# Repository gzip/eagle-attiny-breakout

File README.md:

# AVR ATtiny85 Development Board

This is a flexible development board for the 8 pin family of AVR ATtiny devices. It's like Arduino's little brother. It can be programmed using [Little Wire](https://github.com/gzip/Little-Wire/tree/master), USBasp, Arduino as ISP, etc.

- Arduino compatible via [Arduino-Tiny](https://code.google.com/p/arduino-tiny/) or [Code Bender](https://codebender.cc/)
- All pins exposed via headers
- Header for external power
- Wide operating voltage - 2.7 - 5.5 volts
- 4 channel power bus with filtering capacitors
- Space for an optional resonator
- Mounting holes
- No LED to save power
- Onboard reset switch

# Availability

Currently available in kit form at [Tindie](https://www.tindie.com/products/gzip/avr-attiny85-development-board-kit/).

# Installing

See [Installing](Installing.md) for driver and environment installation.

# License

This hardware is licensed under [Creative Commons Share Alike](http://creativecommons.org/licenses/by-sa/4.0/).

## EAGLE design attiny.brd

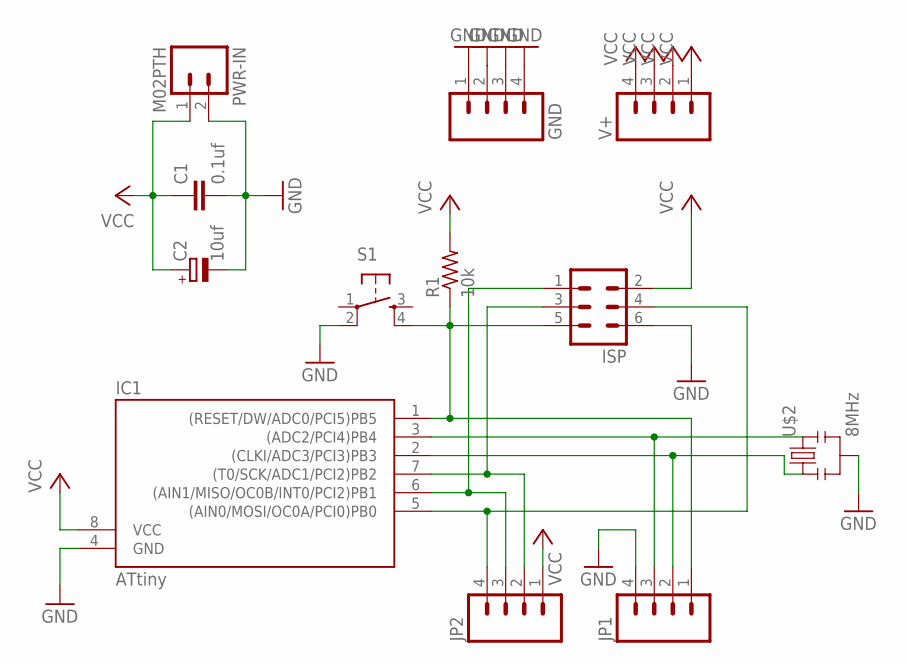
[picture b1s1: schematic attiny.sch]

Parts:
C1: 0.1uf; C025-025X050
C2: 10uf; E2-4
GND: M04PTH; 1X04
IC1: ATtiny; DIL08
ISP: MA03-2
JP1, JP2: M04PTH; 1X04
PWR-IN: M02PTH; 1X02
R1: 10k; 0204/7
S1: TAC_SWITCHPTH; TACTILE-PTH
U$2: 8MHz; RESONATOR-PTH
V+: M04PTH; 1X04

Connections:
GND: C1.2, C2.-, GND.1, GND.2, GND.3, GND.4, IC1.4 (GND), ISP.6, JP1.4, PWR-IN.2, S1.2, U$2.2
unnamed: IC1.2 ((CLKI/ADC3/PCI3)PB3), JP1.2, U$2.1
unnamed: IC1.1 ((RESET/DW/ADC0/PCI5)PB5), ISP.5, JP1.1, R1.1, S1.4
unnamed: IC1.7 ((T0/SCK/ADC1/PCI2)PB2), ISP.3, JP2.2
unnamed: IC1.6 ((AIN1/MISO/OC0B/INT0/PCI2)PB1), ISP.1, JP2.3
unnamed: IC1.3 ((ADC2/PCI4)PB4), JP1.3, U$2.3
unnamed: IC1.5 ((AIN0/MOSI/OC0A/PCI0)PB0), ISP.4, JP2.4
VCC: C1.1, C2.+, IC1.8 (VCC), ISP.2, JP2.1, PWR-IN.1, R1.2, V+.1, V+.2, V+.3, V+.4

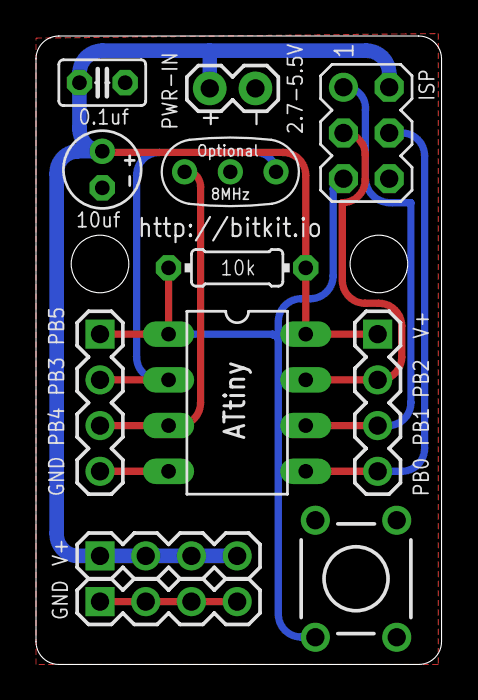
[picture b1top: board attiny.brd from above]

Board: 2 copper layers, 22.5 x 34.9 mm, 12 parts (0 on the bottom side), 8 nets.

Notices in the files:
parts and their libraries:
SparkFun-Connectors: Licensing: Creative Commons ShareAlike 4.0 International - https://creativecommons.org/licenses/by-sa/4.0
